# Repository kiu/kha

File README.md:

# kha

Overengineered Modular RS-485 Multi-Master 19" Subrack Home Control

## Repository

<sup>Hint: "bgt" is German for [Baugruppenträger](https://de.wikipedia.org/wiki/Baugruppentr%C3%A4ger) translating to subrack assembly</sup>

- [datasheets](datasheets/): Datasheets of used components and rack dimensions / layouts
- [kha-bgt-misc](kha-bgt-misc/): Generic subrack modules
- [kha-bgt-rack](kha-bgt-rack/): 19" rack assembly
- [kha-bgt-subrack](kha-bgt-subrack/): Subrack modules
- [kha-boot.X](kha-boot.X/): Bootloader used by all devices ([main.c](kha-boot.X/main.c))
- [kha-common.X](kha-common.X/): Protocol stack used by all devices ([kha-stack.c](kha-common.X/kha-stack.c) / [kha-stack.h](kha-common.X/kha-stack.h) / [kha-constants.h](kha-common.X/kha-constants.h))
- [kha-nodes](kha-nodes/): Bus nodes
- [superseded](superseded/): Superseded ideas and failed hardware revisions
- [tools](tools/): Helper scripts to e.g. generate userrow data
- [kha-bom-collection.pdf](kha-bom-collection.pdf) / [.ods](kha-bom-collection.ods): Not exactly a Bill-of-Materials rather a collection of most components used
- [kha-protocol.pdf](kha-protocol.pdf) / [.ods](kha-protocol.ods): Protocol stack definitions

## Protocol

RS-485 at 500 kbaud (8N1), half duplex, every node may send. Commands, addresses and registers are listed in
[kha-protocol.ods](kha-protocol.ods).

### Frame

```
0x42 0x99 <len> <from> <to> <cmd> <payload ...> <crc>
```

- `0x42 0x99` starts a frame. Inside a frame every `0x42` is followed by an extra `0x66`, so `0x42 0x99` is
  always a start. The escape bytes are not counted and not part of the CRC.
- `len` counts len, from, to, cmd, payload and crc: 5 + payload, payload up to 67 bytes.
- CRC-8 (polynomial 0x31, init 0xFF, no final XOR) over all bytes from `len` to the last byte before the CRC.

### Bus access

- The stack counts 100 µs ticks on TCB2, which is reserved for the stack. Every falling edge on RX resets the
  count.
- A node sends once the bus has been quiet for 10 + its own address ticks (1 ms + address × 100 µs). Addresses
  are unique, so no two nodes wait for the same slot.
- After sending, a node waits once for the longest slot (10 + 0xF0 ticks), so the others get their turn first.
- The bootloader commands F9–FC skip the slot wait to keep flashing fast: send TX off (F0) to the other
  nodes before flashing.

### Firmware

- Flash: bootloader at 0x0000–0x3FFF, app at 0x4000–0xFFFF. At every boot a node computes a CRC-32 over
  0x4000–0xFFFF (without the final XOR) and reports it with the boot and app versions in its UP (E2) and
  ident (E1).
- Bootloader: after a reset it waits 4 s for bootloader commands (FD keeps it there), then starts the app.
  Brown-out detection at 2.85 V. No lock bits, so UPDI can read and write a node.
- Flashing over the bus: [kha_fw.py](tools/kha-scripts/); via UPDI: [kha_updi.py](tools/kha-scripts/).

## Bus health page

[kha-web](tools/kha-web/) shows the state of every node on a static web page: missing nodes, error
counters, days since the last reboot, and whether nodes of the same board type run the same firmware. A
collector follows the gateway's log passively, keeps the state in SQLite and exports a JSON file for the page.
Screenshot with mock data:

## Videos
Two hour deep dive lecture style video on youtube: https://youtu.be/BUSnTUGKZzc

## Photos

## Misc

- All PCBs use [eAVR](https://github.com/kiu/eAVR/) as connector for AVR flashing
- It all started simple with [lightdesk](https://github.com/kiu/lightdesk/)

## Todo

- Node: LED marquee node
- Node: IrDA bridge (bridging the bus through a window)
- Stack: Combine queued TX commands into single burst?
- Stack: Merge similiar queued TX commands into single command?
- Stack: Process TX commands as incoming RX commands?

## Regrets

- Terrible collision detection / avoidance
- Buck converter capacitor generates audible noise

# License

This project is licensed under the Creative Commons Attribution-NonCommercial 3.0 Unported (CC BY-NC 3.0) license.

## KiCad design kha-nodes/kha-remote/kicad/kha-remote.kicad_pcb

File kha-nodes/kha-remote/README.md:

# kha-remote

433Mhz and IR Remote

## Photos

## Render

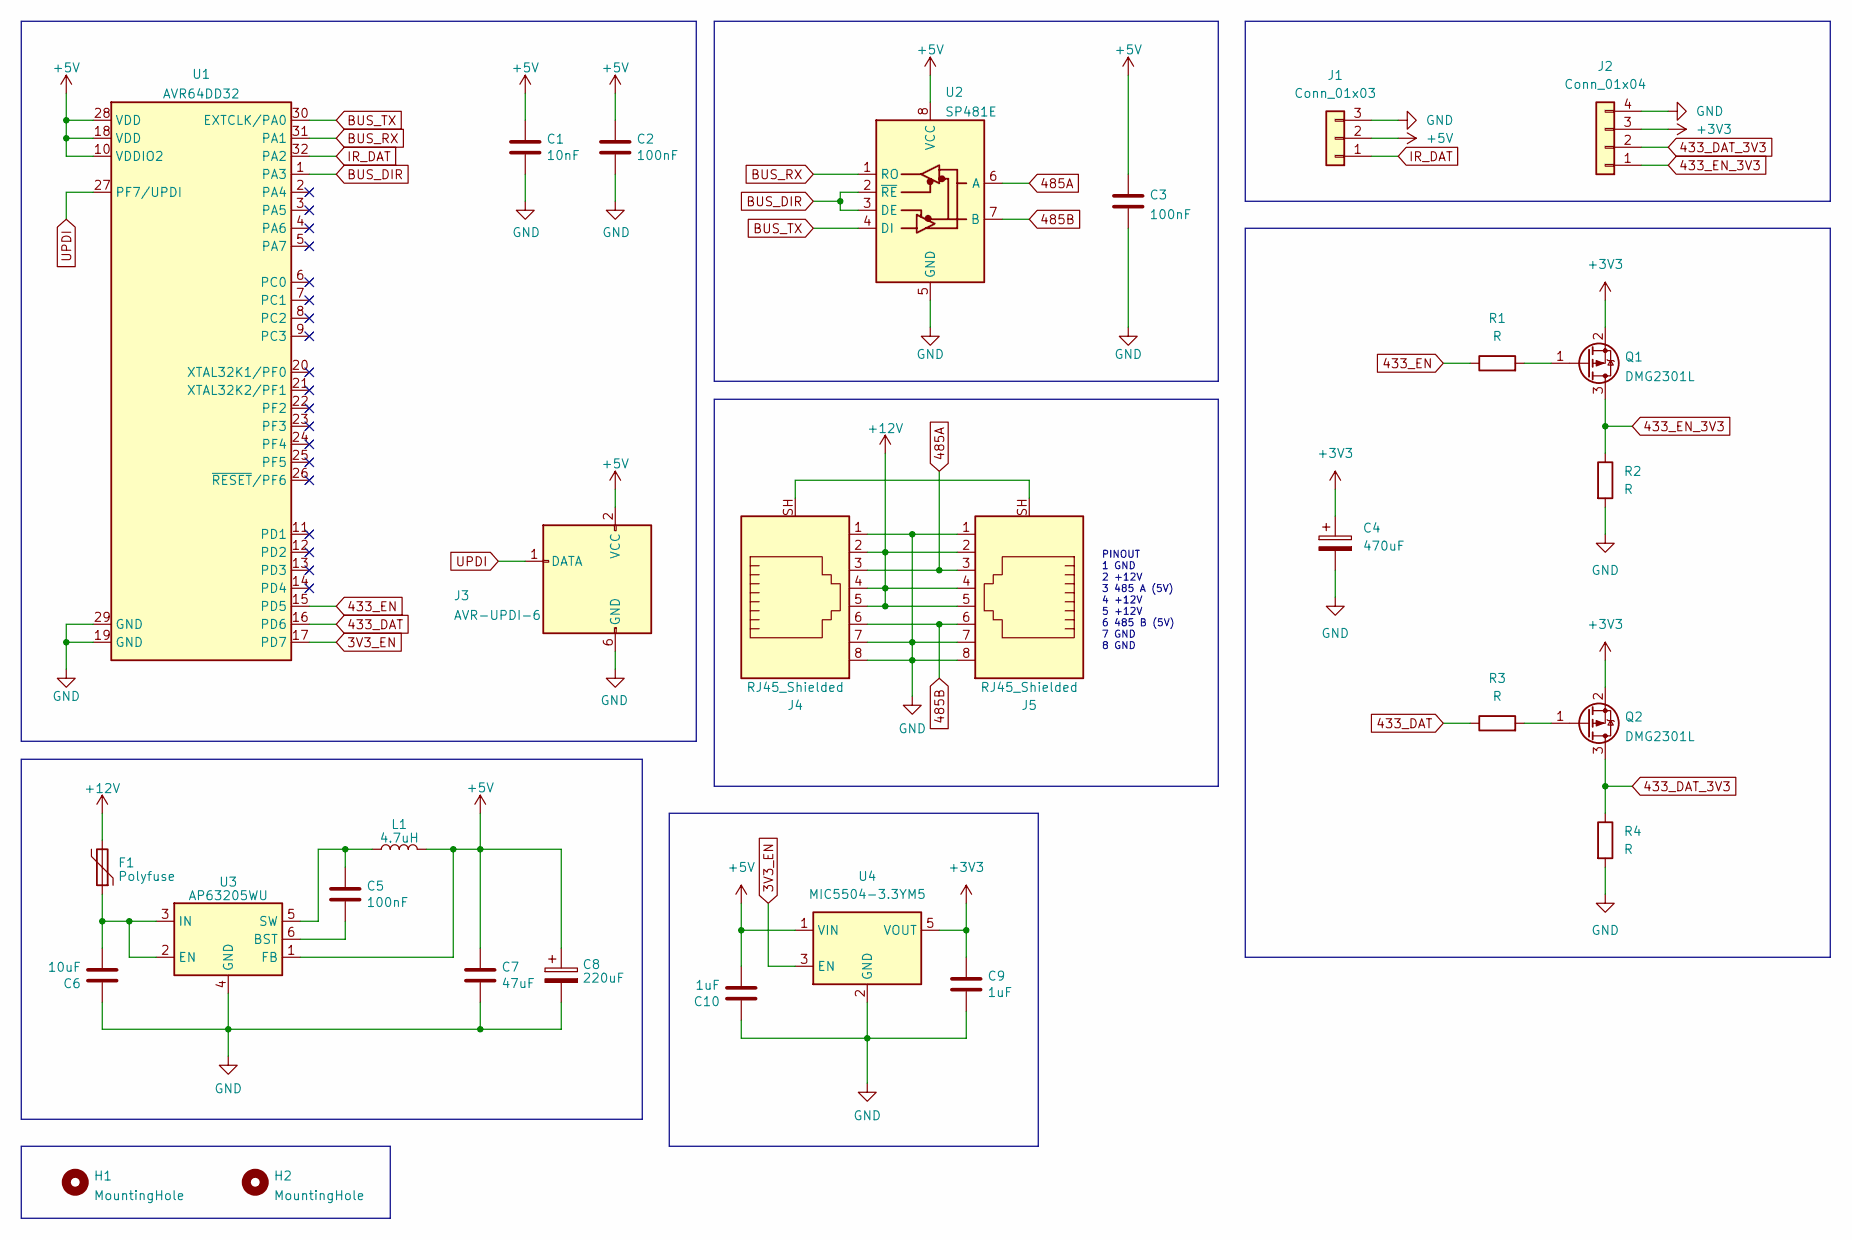
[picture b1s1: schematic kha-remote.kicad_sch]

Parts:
C1: 10nF; C_0805_2012Metric
C2, C3, C5: 100nF; C_0805_2012Metric
C4: 470uF; CP_Elec_6.3x7.7
C6: 10uF; C_0805_2012Metric
C7: 47uF; C_1210_3225Metric
C8: 220uF; CP_EIA-6032-28_Kemet-C
C9, C10: 1uF; C_0805_2012Metric
F1: Polyfuse; Fuse_0805_2012Metric
H1, H2: MountingHole; MountingHole_3.2mm_M3_DIN965
J1: Conn_01x03; TerminalBlock_Phoenix_MKDS-1,5-3-5.08_1x03_P5.08mm_Horizont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
J2: Conn_01x04; PinSocket_1x04_P2.54mm_Vertical
J3: AVR-UPDI-6; eAVR6-UPDI-F
J4, J5: RJ45_Shielded; GDLX-S-88K
L1: 4.7uH; L_1210_3225Metric
Q1, Q2: DMG2301L; SOT-23
R1, R2, R3, R4: R; R_0805_2012Metric
U1: AVR64DD32; TQFP-32_7x7mm_P0.8mm
U2: SP481E; SOIC-8_3.9x4.9mm_P1.27mm
U3: AP63205WU; TSOT-23-6
U4: MIC5504-3.3YM5; SOT-23-5

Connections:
3V3_EN: U1.17 (PD7), U4.3 (EN)
433_DAT: R3.1, U1.16 (PD6)
433_DAT_3V3: J2.2, Q2.3 (D), R4.1
433_EN: R1.1, U1.15 (PD5)
433_EN_3V3: J2.1, Q1.3 (D), R2.1
485A: J4.3, J5.3, U2.6 (A)
485B: J4.6, J5.6, U2.7 (B)
+3V3: C4.1, C9.1, J2.3, Q1.2 (S), Q2.2 (S), U4.5 (VOUT)
+5V: C1.1, C2.1, C3.1, C7.1, C8.1, C10.2, J1.2, J3.2 (VCC), L1.2, U1.10 (VDDIO2), U1.18 (VDD), U1.28 (VDD), U2.8 (VCC), U3.1 (FB), U4.1 (VIN)
+12V: F1.2, J4.2, J4.4, J4.5, J5.2, J5.4, J5.5
BUS_DIR: U1.1 (PA3), U2.2 (~RE), U2.3 (DE)
BUS_RX: U1.31 (PA1), U2.1 (RO)
BUS_TX: U1.30 (EXTCLK/PA0), U2.4 (DI)
GND: C1.2, C2.2, C3.2, C4.2, C6.1, C7.2, C8.2, C9.2, C10.1, J1.3, J2.4, J3.6 (GND), J4.1, J4.7, J4.8, J5.1, J5.7, J5.8, R2.2, R4.2, U1.19 (GND), U1.29 (GND), U2.5 (GND), U3.4 (GND), U4.2 (GND)
IR_DAT: J1.1, U1.32 (PA2)
unnamed: J4.SH, J5.SH
unnamed: Q1.1 (G), R1.2
unnamed: Q2.1 (G), R3.2
unnamed: C5.2, U3.6 (BST)
unnamed: C6.2, F1.1, U3.2 (EN), U3.3 (IN)
unnamed: C5.1, L1.1, U3.5 (SW)
UPDI: J3.1 (DATA), U1.27 (PF7/UPDI)

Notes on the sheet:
PINOUT 1 GND 2 +12V 3 485 A (5V) 4 +12V 5 +12V 6 485 B (5V) 7 GND 8 GND

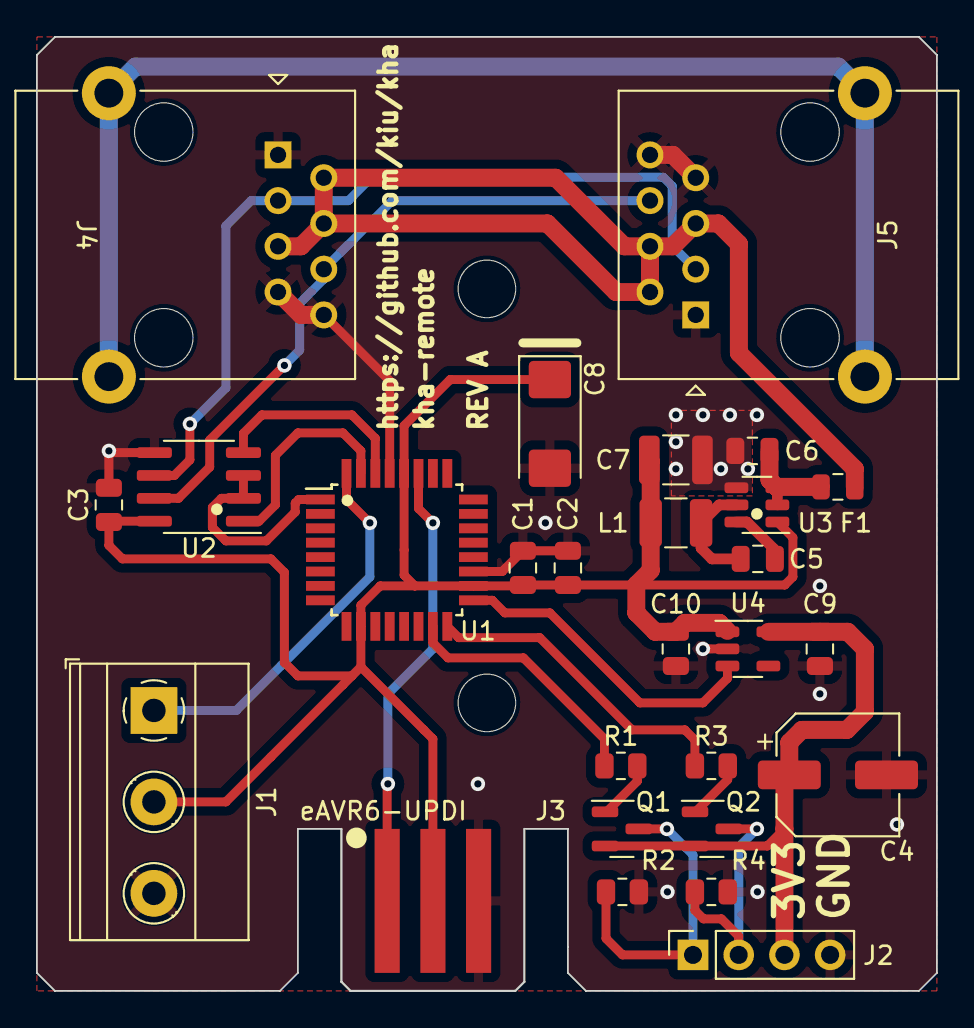
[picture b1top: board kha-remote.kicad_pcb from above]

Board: 2 copper layers, 50.0 x 53.0 mm, 29 parts (0 on the bottom side), 22 nets.

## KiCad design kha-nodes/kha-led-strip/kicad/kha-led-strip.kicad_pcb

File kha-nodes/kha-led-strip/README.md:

# kha-led-strip

LED Strip Node

## Photos

## Render

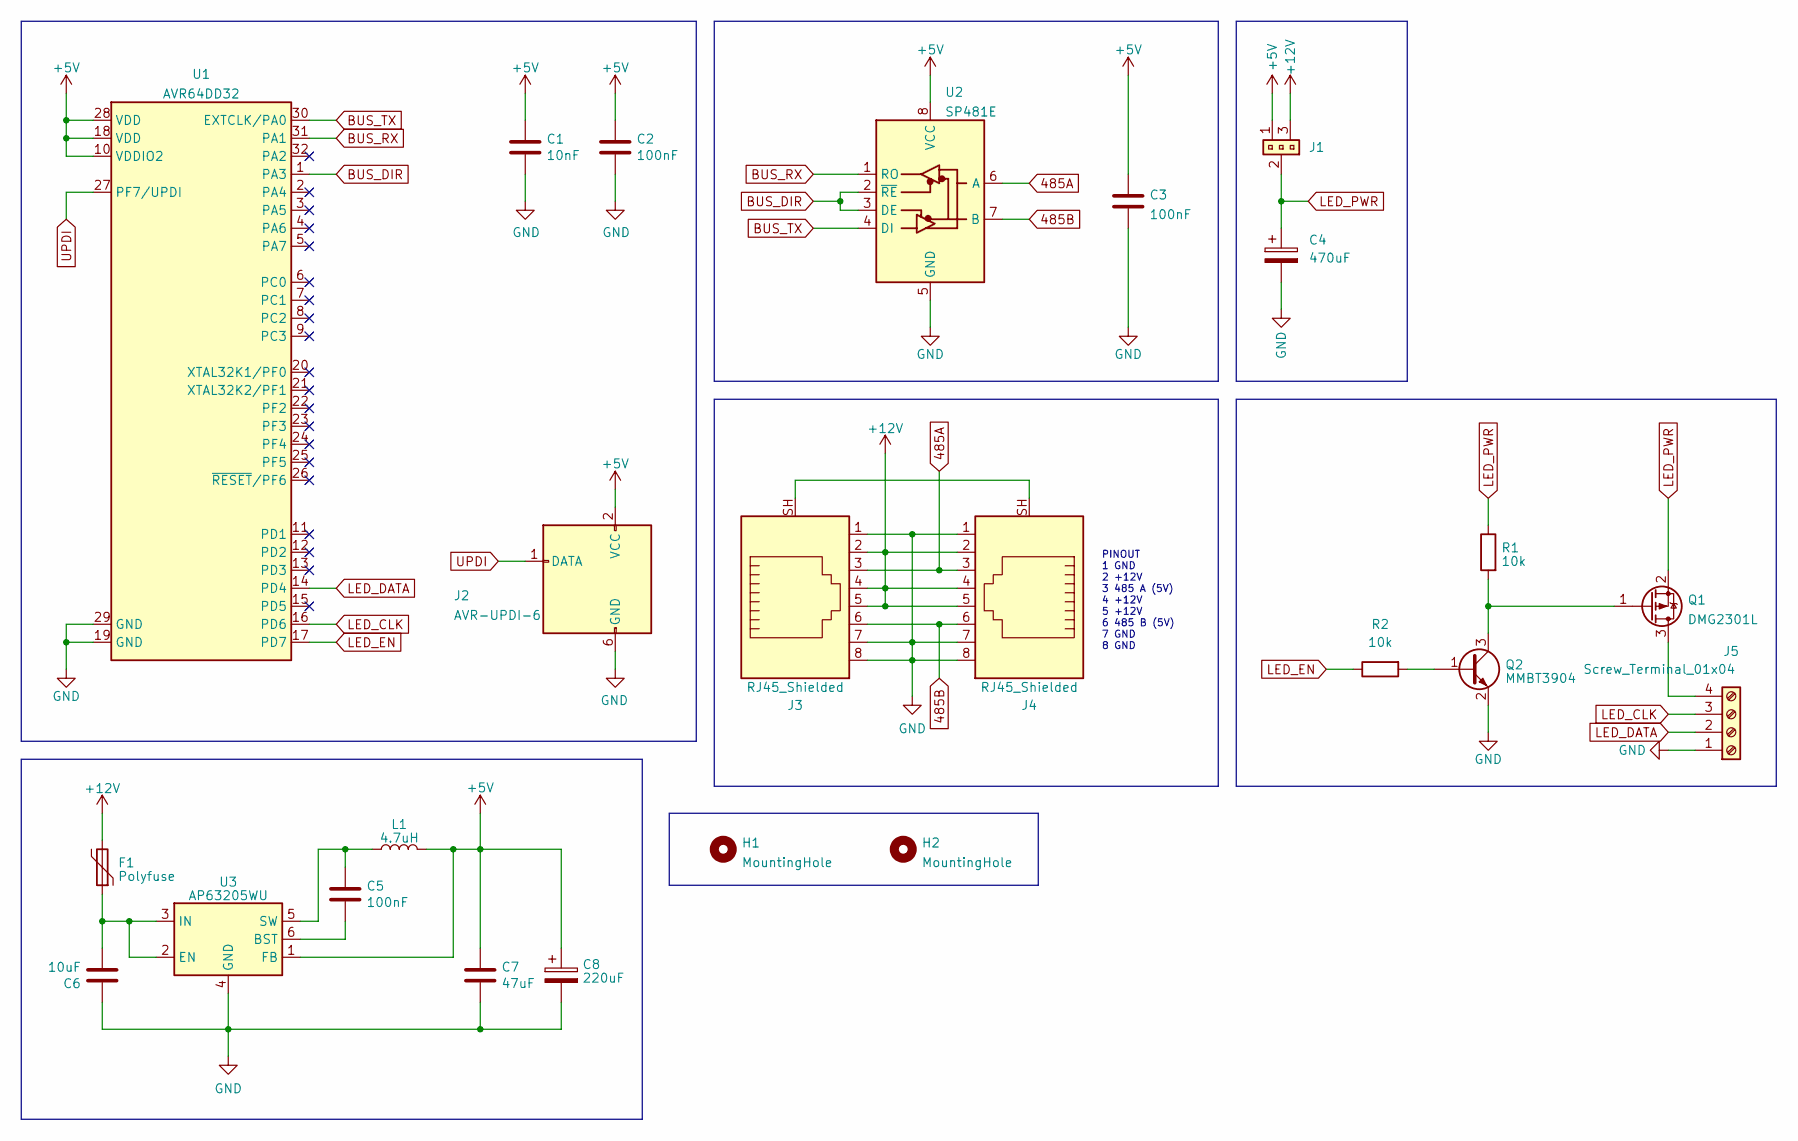
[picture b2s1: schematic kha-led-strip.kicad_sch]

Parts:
C1: 10nF; C_0805_2012Metric
C2, C3, C5: 100nF; C_0805_2012Metric
C4: 470uF; CP_Elec_8x10.5
C6: 10uF; C_0805_2012Metric
C7: 47uF; C_1210_3225Metric
C8: 220uF; CP_EIA-6032-28_Kemet-C
F1: Polyfuse; Fuse_0805_2012Metric
H1, H2: MountingHole; MountingHole_3.2mm_M3_DIN965
J1: 1x03_Jumper; PinHeader_1x03_P2.54mm_Vertical
J2: AVR-UPDI-6; eAVR6-UPDI-F
J3, J4: RJ45_Shielded; GDLX-S-88K
J5: Screw_Terminal_01x04; TerminalBlock_Phoenix_MKDS-1,5-4-5.08_1x04_P5.08mm_Horizont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
L1: 4.7uH; L_1210_3225Metric
Q1: DMG2301L; SOT-23
Q2: MMBT3904; SOT-23
R1, R2: 10k; R_0805_2012Metric
U1: AVR64DD32; TQFP-32_7x7mm_P0.8mm
U2: SP481E; SOIC-8_3.9x4.9mm_P1.27mm
U3: AP63205WU; TSOT-23-6

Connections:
485A: J3.3, J4.3, U2.6 (A)
485B: J3.6, J4.6, U2.7 (B)
+5V: C1.1, C2.1, C3.1, C7.1, C8.1, J1.1, J2.2 (VCC), L1.2, U1.10 (VDDIO2), U1.18 (VDD), U1.28 (VDD), U2.8 (VCC), U3.1 (FB)
+12V: F1.2, J1.3, J3.2, J3.4, J3.5, J4.2, J4.4, J4.5
BUS_DIR: U1.1 (PA3), U2.2 (~RE), U2.3 (DE)
BUS_RX: U1.31 (PA1), U2.1 (RO)
BUS_TX: U1.30 (EXTCLK/PA0), U2.4 (DI)
GND: C1.2, C2.2, C3.2, C4.2, C6.1, C7.2, C8.2, J2.6 (GND), J3.1, J3.7, J3.8, J4.1, J4.7, J4.8, J5.1, Q2.2 (E), U1.19 (GND), U1.29 (GND), U2.5 (GND), U3.4 (GND)
LED_CLK: J5.3, U1.16 (PD6)
LED_DATA: J5.2, U1.14 (PD4)
LED_EN: R2.1, U1.17 (PD7)
LED_PWR: C4.1, J1.2, Q1.2 (S), R1.1
unnamed: J3.SH, J4.SH
unnamed: J5.4, Q1.3 (D)
unnamed: Q1.1 (G), Q2.3 (C), R1.2
unnamed: Q2.1 (B), R2.2
unnamed: C5.2, U3.6 (BST)
unnamed: C6.2, F1.1, U3.2 (EN), U3.3 (IN)
unnamed: C5.1, L1.1, U3.5 (SW)
UPDI: J2.1 (DATA), U1.27 (PF7/UPDI)

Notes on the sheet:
PINOUT 1 GND 2 +12V 3 485 A (5V) 4 +12V 5 +12V 6 485 B (5V) 7 GND 8 GND

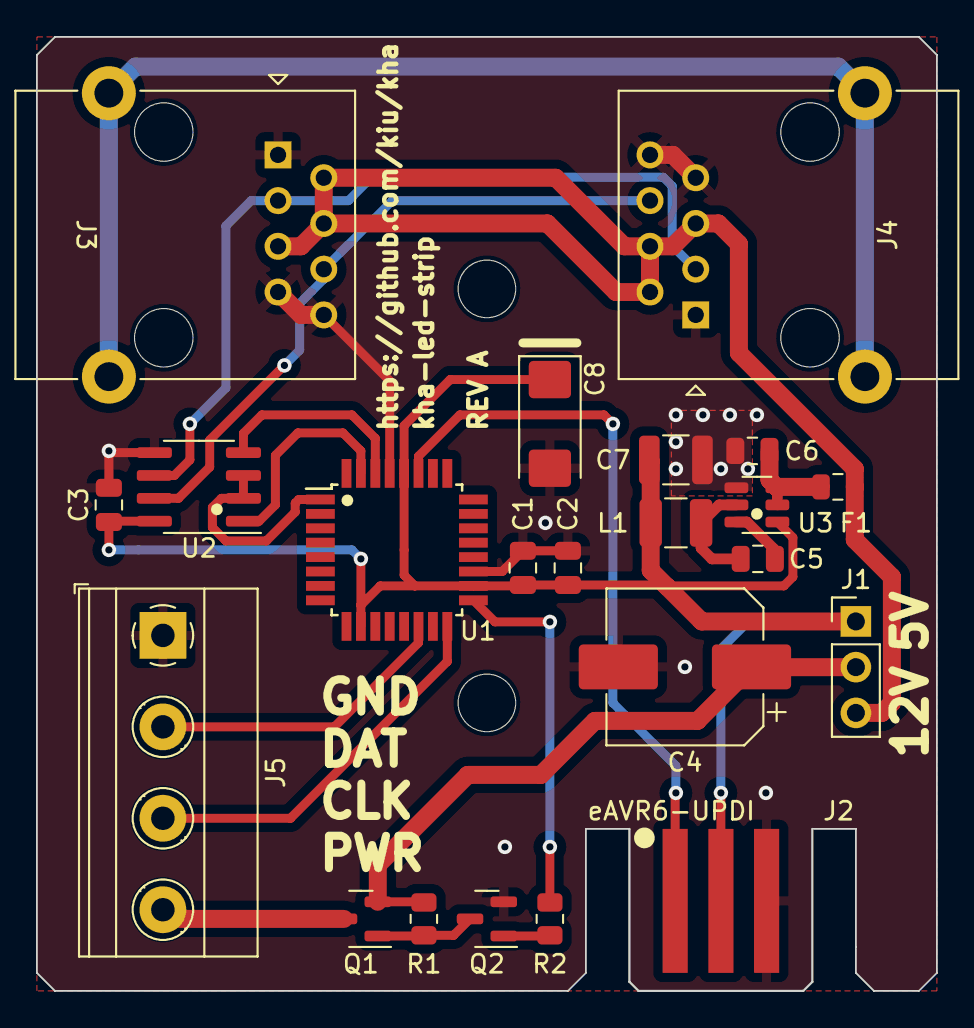
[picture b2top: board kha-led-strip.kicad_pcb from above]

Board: 2 copper layers, 50.0 x 53.0 mm, 24 parts (0 on the bottom side), 20 nets.

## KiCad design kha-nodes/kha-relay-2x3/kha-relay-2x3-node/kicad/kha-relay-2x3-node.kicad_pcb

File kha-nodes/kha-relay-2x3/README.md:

# kha-relay-2x3

Mains Power Relay

## Photos

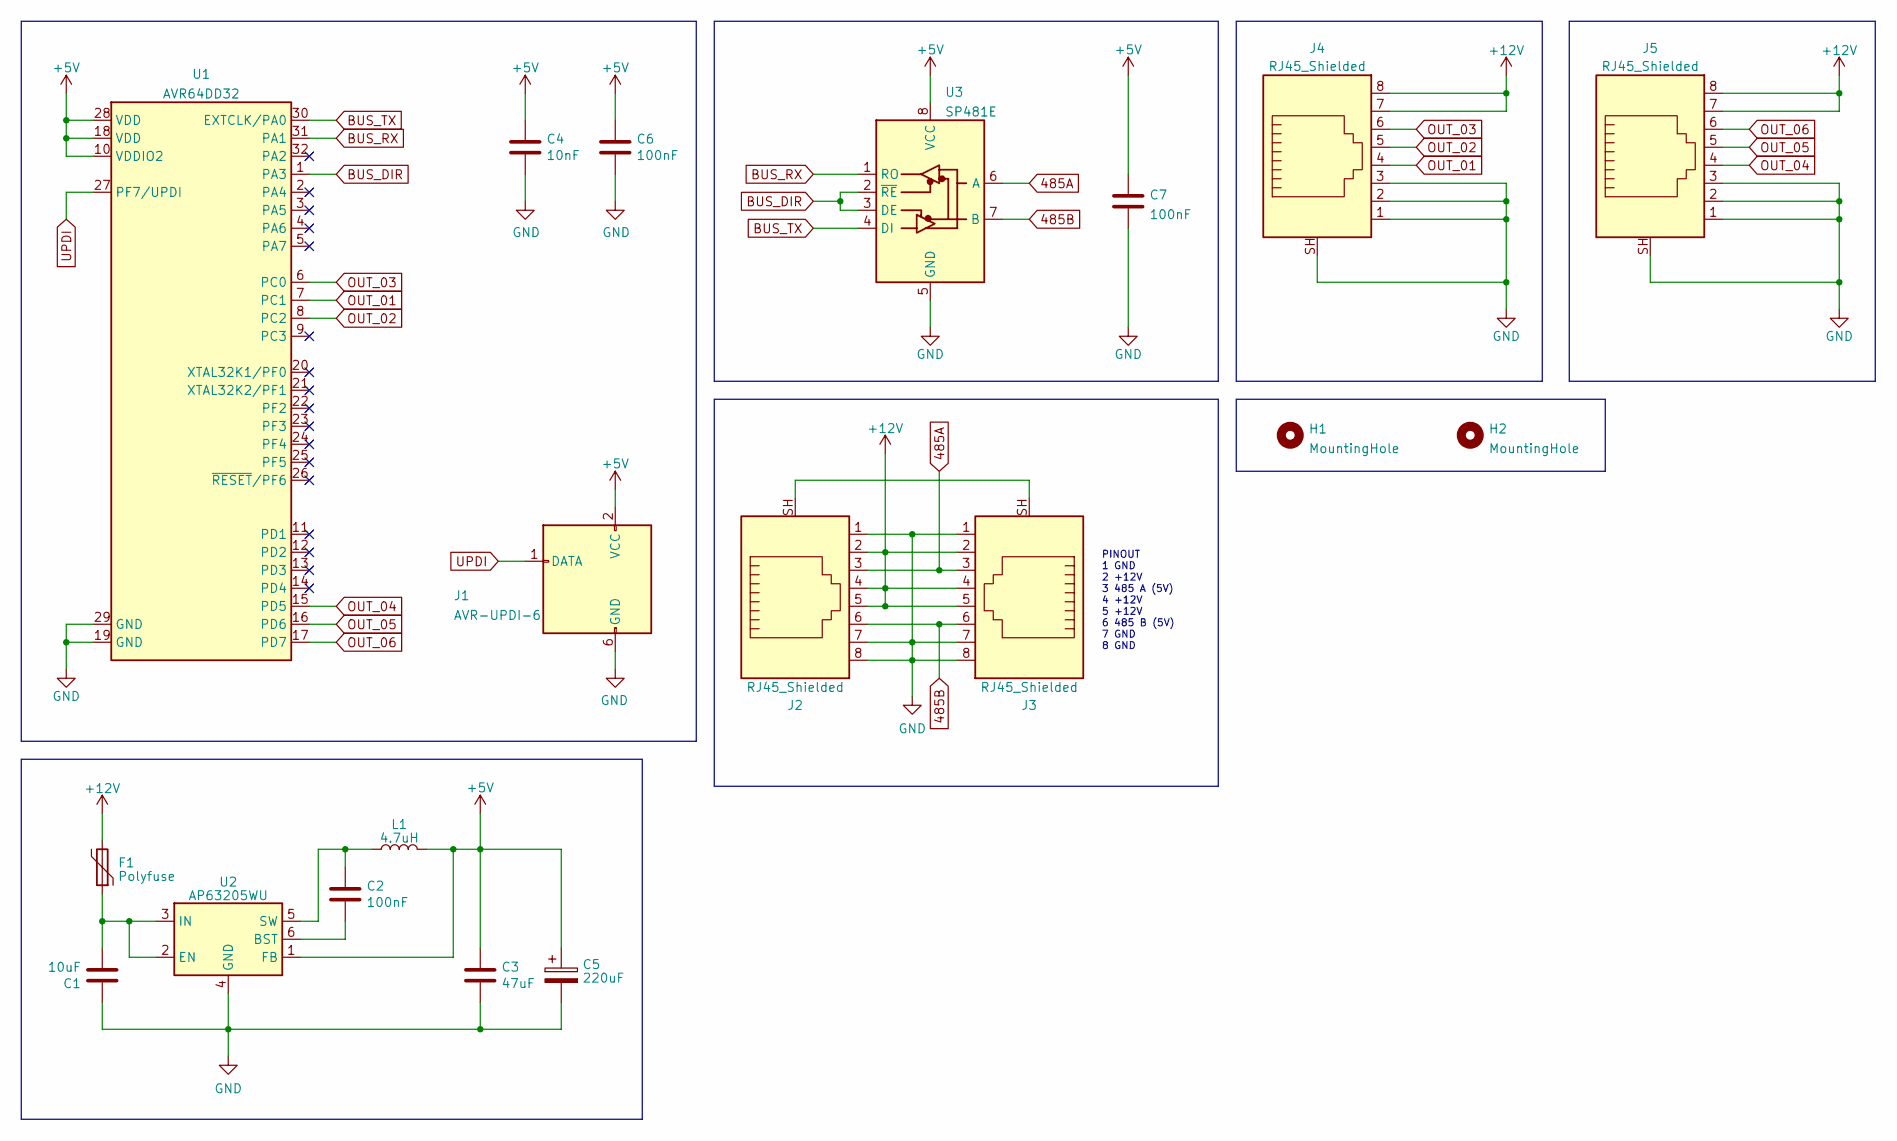
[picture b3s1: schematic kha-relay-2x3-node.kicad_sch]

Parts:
C1: 10uF; C_0805_2012Metric
C2, C6, C7: 100nF; C_0805_2012Metric
C3: 47uF; C_1210_3225Metric
C4: 10nF; C_0805_2012Metric
C5: 220uF; CP_EIA-6032-28_Kemet-C
F1: Polyfuse; Fuse_0805_2012Metric
H1, H2: MountingHole; MountingHole_3.2mm_M3_DIN965
J1: AVR-UPDI-6; eAVR6-UPDI-F
J2, J3, J4, J5: RJ45_Shielded; GDLX-S-88K
L1: 4.7uH; L_1210_3225Metric
U1: AVR64DD32; TQFP-32_7x7mm_P0.8mm
U2: AP63205WU; TSOT-23-6
U3: SP481E; SOIC-8_3.9x4.9mm_P1.27mm

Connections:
485A: J2.3, J3.3, U3.6 (A)
485B: J2.6, J3.6, U3.7 (B)
+5V: C3.1, C4.1, C5.1, C6.1, C7.1, J1.2 (VCC), L1.2, U1.10 (VDDIO2), U1.18 (VDD), U1.28 (VDD), U2.1 (FB), U3.8 (VCC)
+12V: F1.2, J2.2, J2.4, J2.5, J3.2, J3.4, J3.5, J4.7, J4.8, J5.7, J5.8
BUS_DIR: U1.1 (PA3), U3.2 (~RE), U3.3 (DE)
BUS_RX: U1.31 (PA1), U3.1 (RO)
BUS_TX: U1.30 (EXTCLK/PA0), U3.4 (DI)
GND: C1.1, C3.2, C4.2, C5.2, C6.2, C7.2, J1.6 (GND), J2.1, J2.7, J2.8, J3.1, J3.7, J3.8, J4.1, J4.2, J4.3, J4.SH, J5.1, J5.2, J5.3, J5.SH, U1.19 (GND), U1.29 (GND), U2.4 (GND), U3.5 (GND)
unnamed: J2.SH, J3.SH
unnamed: C2.2, U2.6 (BST)
unnamed: C1.2, F1.1, U2.2 (EN), U2.3 (IN)
unnamed: C2.1, L1.1, U2.5 (SW)
OUT_01: J4.4, U1.7 (PC1)
OUT_02: J4.5, U1.8 (PC2)
OUT_03: J4.6, U1.6 (PC0)
OUT_04: J5.4, U1.15 (PD5)
OUT_05: J5.5, U1.16 (PD6)
OUT_06: J5.6, U1.17 (PD7)
UPDI: J1.1 (DATA), U1.27 (PF7/UPDI)

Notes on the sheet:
PINOUT 1 GND 2 +12V 3 485 A (5V) 4 +12V 5 +12V 6 485 B (5V) 7 GND 8 GND

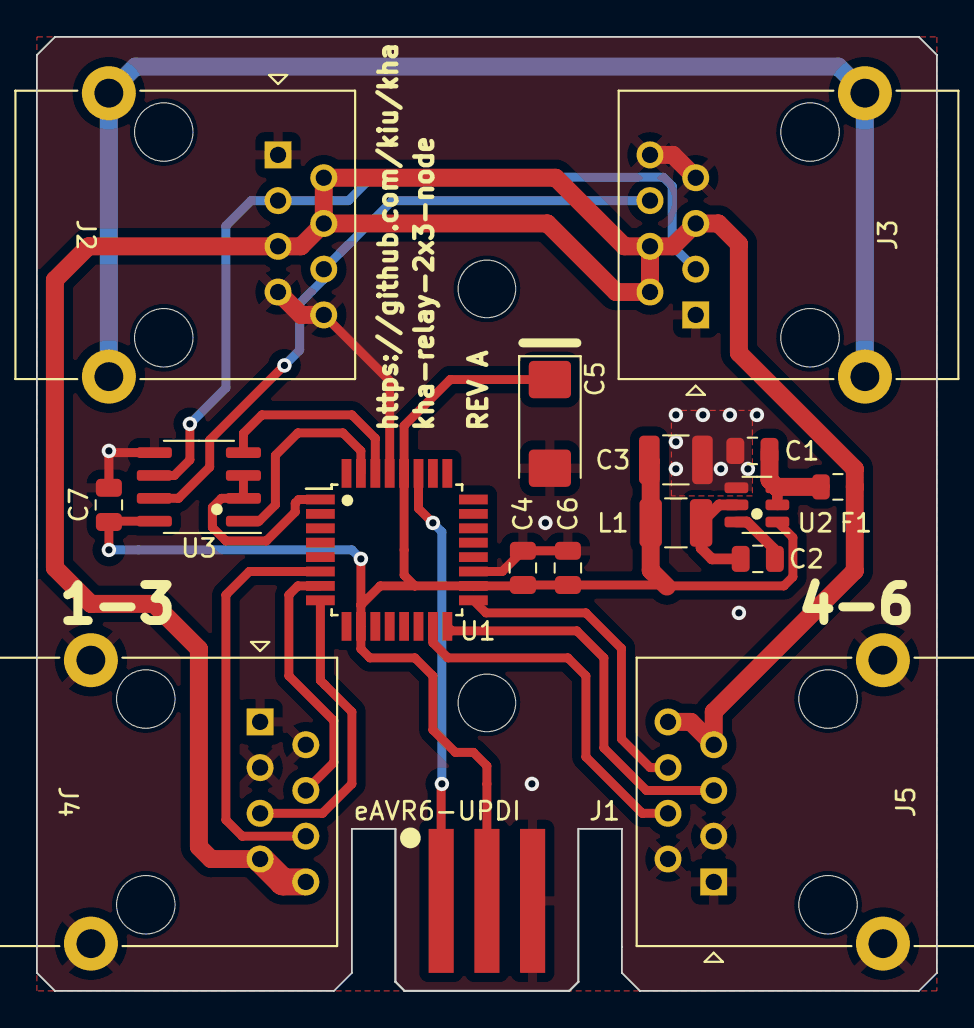
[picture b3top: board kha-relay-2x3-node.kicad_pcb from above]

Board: 2 copper layers, 50.0 x 53.0 mm, 19 parts (0 on the bottom side), 19 nets.

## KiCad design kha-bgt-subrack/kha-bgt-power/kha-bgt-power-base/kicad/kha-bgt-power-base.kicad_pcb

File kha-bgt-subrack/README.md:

# kha-bgt-subrack

Subrack modules

## Photos

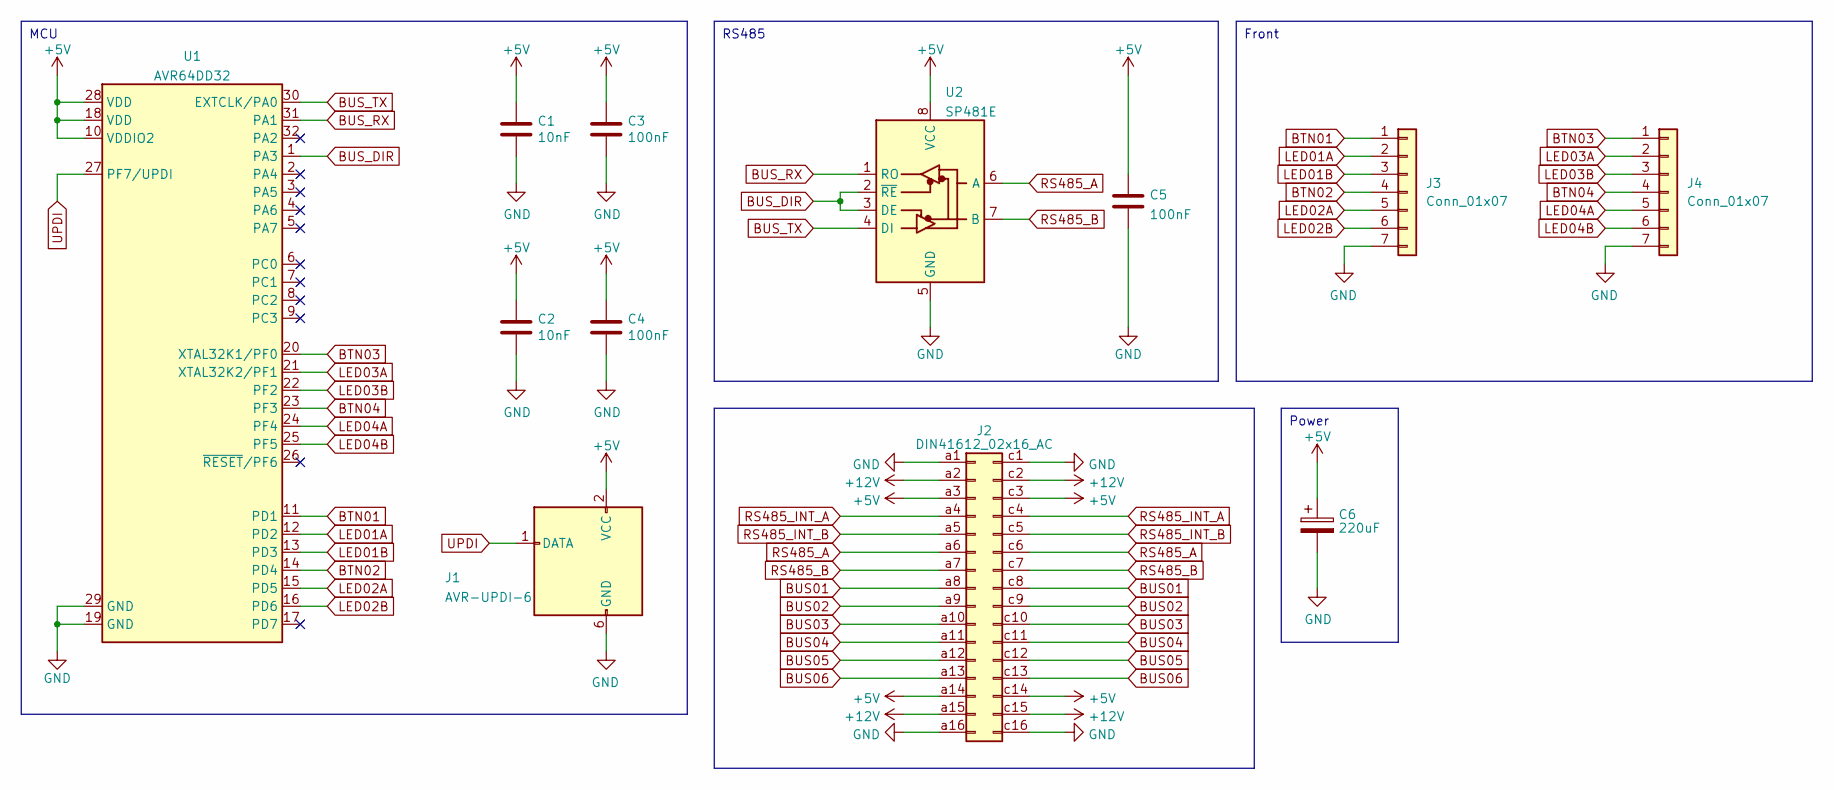
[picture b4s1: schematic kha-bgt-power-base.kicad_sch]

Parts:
C1, C2: 10nF; C_0805_2012Metric
C3, C4, C5: 100nF; C_0805_2012Metric
C6: 220uF; CP_EIA-6032-28_Kemet-C
J1: AVR-UPDI-6; eAVR6-UPDI-F
J2: DIN41612_02x16_AC; DIN41612_C2_2x16_Male_Horizontal_THT
J3, J4: Conn_01x07; JST_PH_B7B-PH-K_1x07_P2.00mm_Vertical
U1: AVR64DD32; TQFP-32_7x7mm_P0.8mm
U2: SP481E; SOIC-8_3.9x4.9mm_P1.27mm

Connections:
+5V: C1.1, C2.1, C3.1, C4.1, C5.1, C6.1, J1.2 (VCC), J2.a3, J2.a14, J2.c3, J2.c14, U1.10 (VDDIO2), U1.18 (VDD), U1.28 (VDD), U2.8 (VCC)
+12V: J2.a2, J2.a15, J2.c2, J2.c15
BTN01: J3.1, U1.11 (PD1)
BTN02: J3.4, U1.14 (PD4)
BTN03: J4.1, U1.20 (XTAL32K1/PF0)
BTN04: J4.4, U1.23 (PF3)
BT_CON: U1.5 (PA7)
BT_LNK: U1.8 (PC2)
BT_RX: U1.6 (PC0)
BT_TX: U1.7 (PC1)
BUS01: J2.a8, J2.c8
BUS02: J2.a9, J2.c9
BUS03: J2.a10, J2.c10
BUS04: J2.a11, J2.c11
BUS05: J2.a12, J2.c12
BUS06: J2.a13, J2.c13
BUS_DIR: U1.1 (PA3), U2.2 (~RE), U2.3 (DE)
BUS_RX: U1.31 (PA1), U2.1 (RO)
BUS_TX: U1.30 (EXTCLK/PA0), U2.4 (DI)
GND: C1.2, C2.2, C3.2, C4.2, C5.2, C6.2, J1.6 (GND), J2.a1, J2.a16, J2.c1, J2.c16, J3.7, J4.7, U1.19 (GND), U1.29 (GND), U2.5 (GND)
LED01A: J3.2, U1.12 (PD2)
LED01B: J3.3, U1.13 (PD3)
LED02A: J3.5, U1.15 (PD5)
LED02B: J3.6, U1.16 (PD6)
LED03A: J4.2, U1.21 (XTAL32K2/PF1)
LED03B: J4.3, U1.22 (PF2)
LED04A: J4.5, U1.24 (PF4)
LED04B: J4.6, U1.25 (PF5)
RS485_A: J2.a6, J2.c6, U2.6 (A)
RS485_B: J2.a7, J2.c7, U2.7 (B)
RS485_INT_A: J2.a4, J2.c4
RS485_INT_B: J2.a5, J2.c5
SR01: U1.4 (PA6)
SR02: U1.2 (PA4)
SR03: U1.3 (PA5)
S_BT_VCC: U1.9 (PC3)
UPDI: J1.1 (DATA), U1.27 (PF7/UPDI)

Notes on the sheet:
Front
Power
RS485
MCU

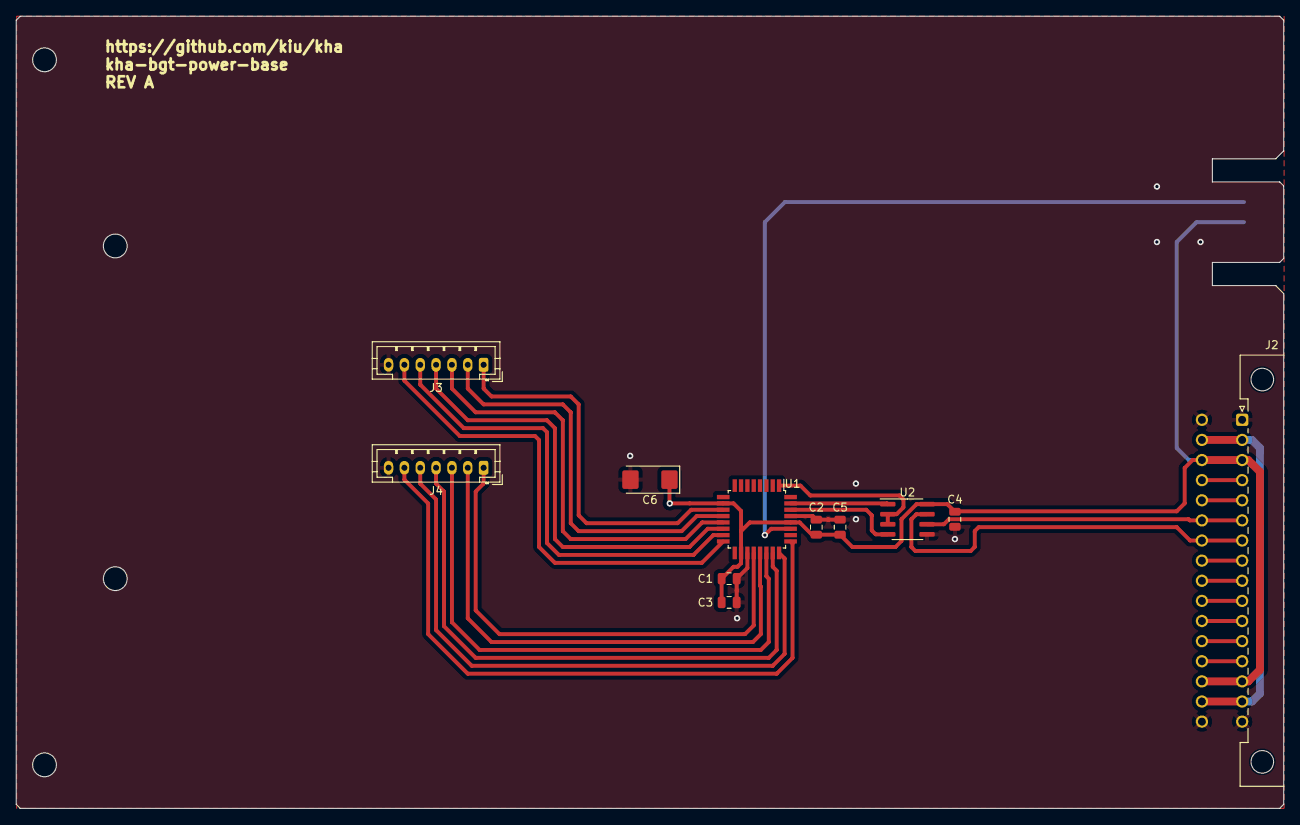
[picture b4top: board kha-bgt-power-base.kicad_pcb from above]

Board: 2 copper layers, 160.0 x 100.0 mm, 12 parts (1 on the bottom side), 29 nets.

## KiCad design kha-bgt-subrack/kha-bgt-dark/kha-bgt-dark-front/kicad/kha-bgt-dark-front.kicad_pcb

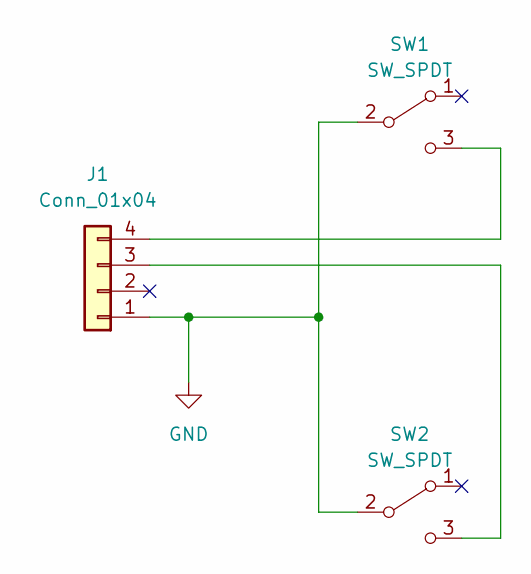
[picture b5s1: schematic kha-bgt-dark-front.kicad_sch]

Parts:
J1: Conn_01x04; JST_PH_B4B-PH-SM4-TB_1x04-1MP_P2.00mm_Vertical
SW1, SW2: SW_SPDT; PB86

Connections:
GND: J1.1, SW1.2 (B), SW2.2 (B)
unnamed: J1.3, SW2.3 (C)
unnamed: J1.4, SW1.3 (C)

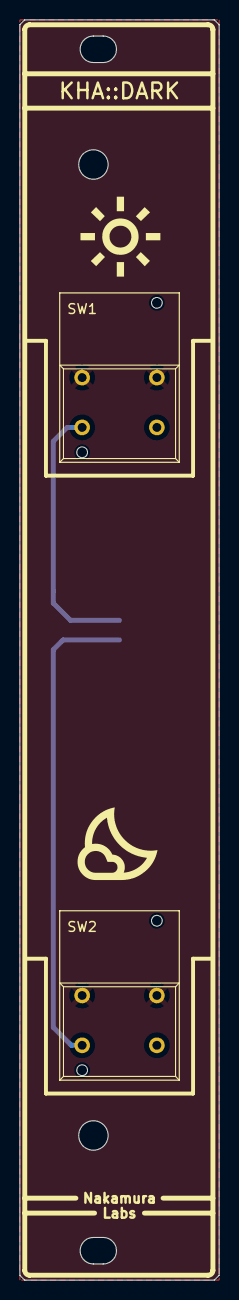
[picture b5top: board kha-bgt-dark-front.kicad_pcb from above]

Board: 2 copper layers, 20.3 x 128.5 mm, 3 parts (1 on the bottom side), 3 nets.

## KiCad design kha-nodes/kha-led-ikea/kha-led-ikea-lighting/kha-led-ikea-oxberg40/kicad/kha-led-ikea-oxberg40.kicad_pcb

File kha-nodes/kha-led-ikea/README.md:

# kha-led-ikea-lighting

IKEA LED Panels and Termination

## Photos

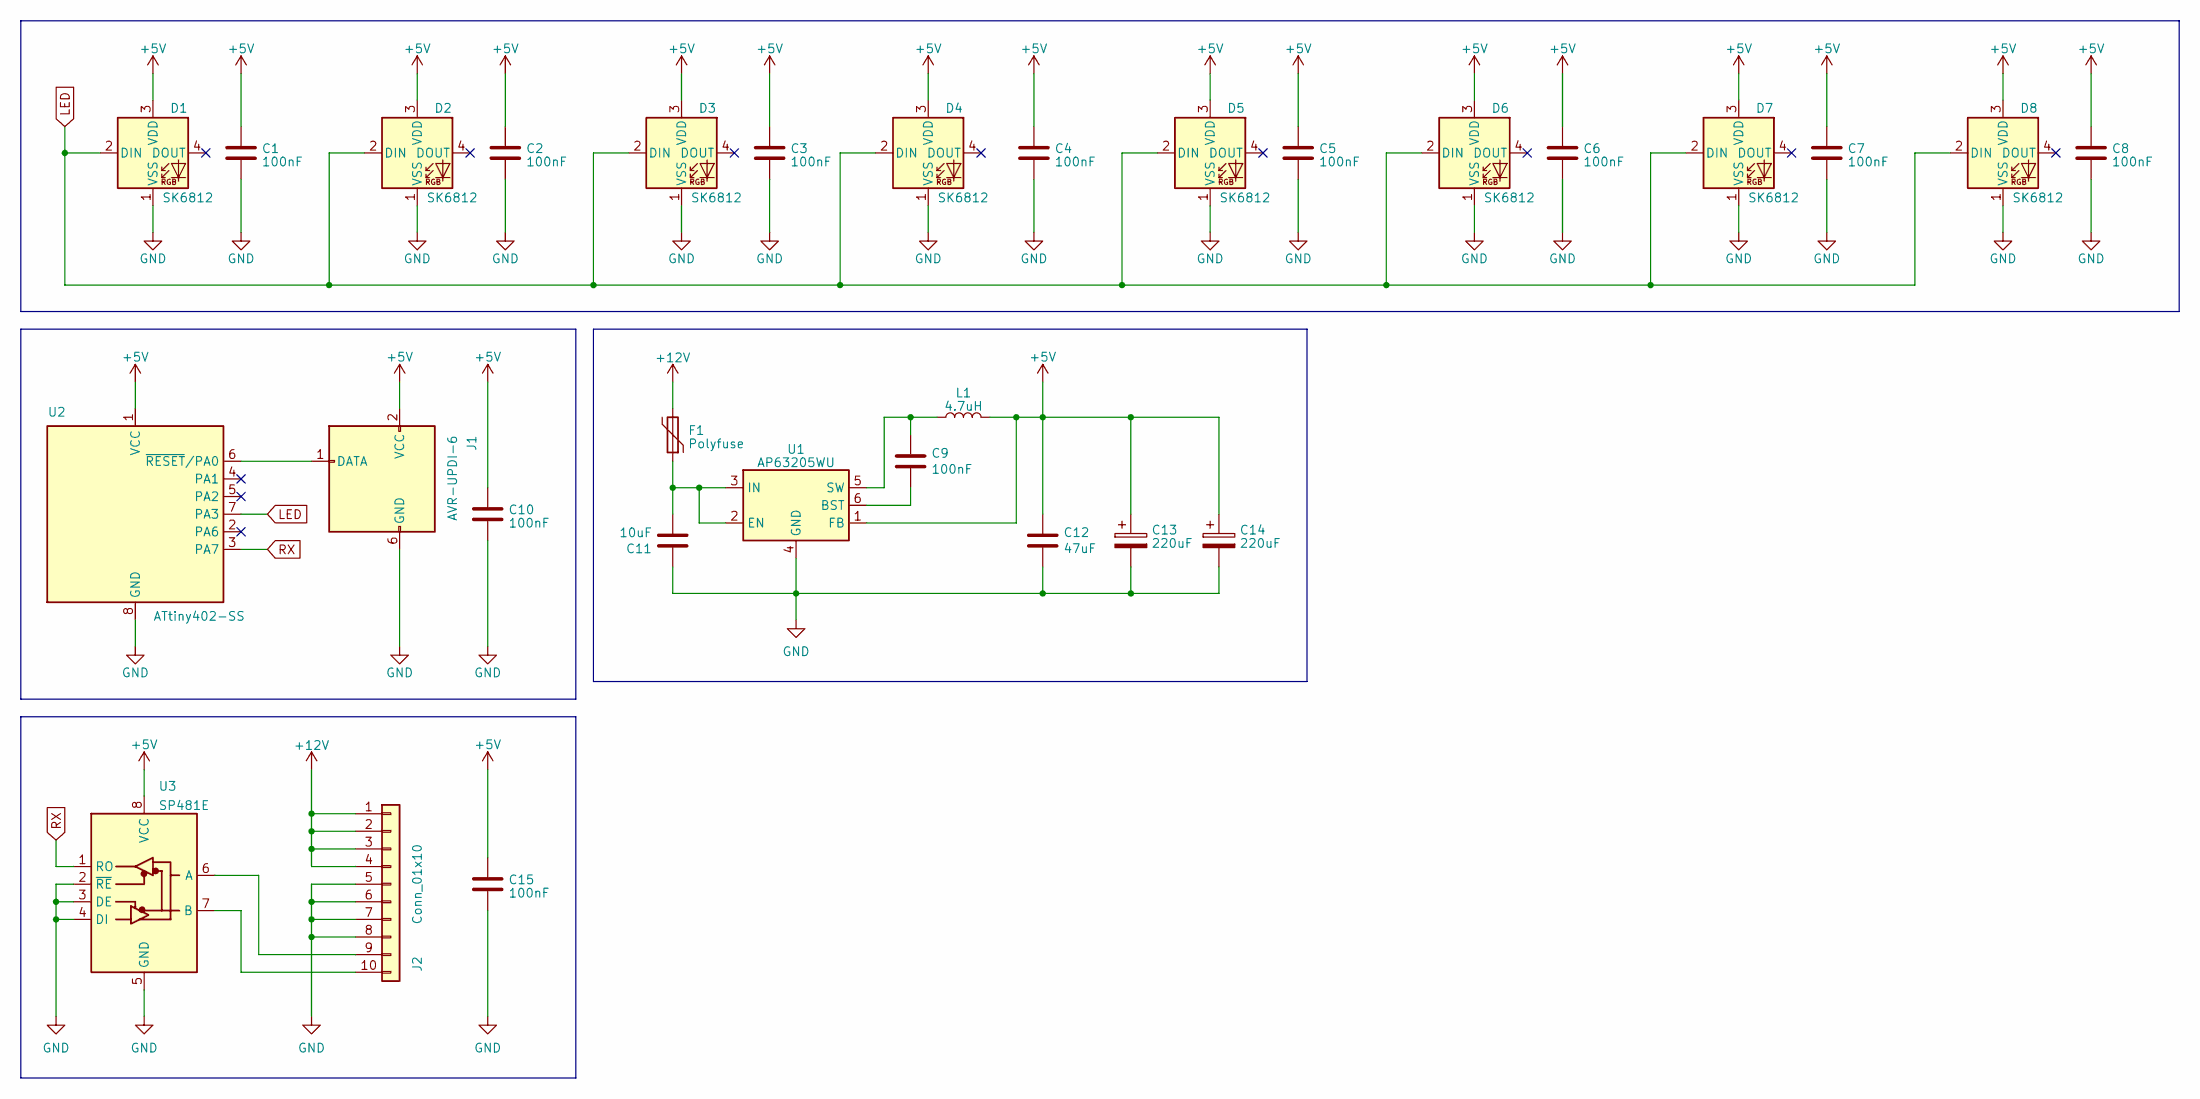
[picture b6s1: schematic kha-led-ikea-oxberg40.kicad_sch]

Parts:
C1, C2, C3, C4, C5, C6, C7, C8, C9, C10, C15: 100nF; C_0805_2012Metric
C11: 10uF; C_0805_2012Metric
C12: 47uF; C_1210_3225Metric
C13, C14: 220uF; CP_EIA-6032-28_Kemet-C
D1, D2, D3, D4, D5, D6, D7, D8: SK6812; LED_SK6812_PLCC4_5.0x5.0mm_P3.2mm
F1: Polyfuse; Fuse_0805_2012Metric
J1: AVR-UPDI-6; IDC-Header_2x03_P2.54mm_Vertical_SMD
J2: Conn_01x10; IDC-Header_2x05_P2.54mm_Vertical_SMD
L1: 4.7uH; L_1210_3225Metric
U1: AP63205WU; TSOT-23-6
U2: ATtiny402-SS; SOIC-8_3.9x4.9mm_P1.27mm
U3: SP481E; SOIC-8_3.9x4.9mm_P1.27mm

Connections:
+5V: C1.1, C2.1, C3.1, C4.1, C5.1, C6.1, C7.1, C8.1, C10.1, C12.1, C13.1, C14.1, C15.1, D1.3 (VDD), D2.3 (VDD), D3.3 (VDD), D4.3 (VDD), D5.3 (VDD), D6.3 (VDD), D7.3 (VDD), D8.3 (VDD), J1.2 (VCC), L1.2, U1.1 (FB), U2.1 (VCC), U3.8 (VCC)
+12V: F1.2, J2.1, J2.2, J2.3, J2.4
GND: C1.2, C2.2, C3.2, C4.2, C5.2, C6.2, C7.2, C8.2, C10.2, C11.1, C12.2, C13.2, C14.2, C15.2, D1.1 (VSS), D2.1 (VSS), D3.1 (VSS), D4.1 (VSS), D5.1 (VSS), D6.1 (VSS), D7.1 (VSS), D8.1 (VSS), J1.6 (GND), J2.5, J2.6, J2.7, J2.8, U1.4 (GND), U2.8 (GND), U3.2 (~RE), U3.3 (DE), U3.4 (DI), U3.5 (GND)
LED: D1.2 (DIN), D2.2 (DIN), D3.2 (DIN), D4.2 (DIN), D5.2 (DIN), D6.2 (DIN), D7.2 (DIN), D8.2 (DIN), U2.7 (PA3)
unnamed: J1.1 (DATA), U2.6 (~RESET/PA0)
unnamed: J2.9, U3.6 (A)
unnamed: J2.10, U3.7 (B)
unnamed: C9.2, U1.6 (BST)
unnamed: C11.2, F1.1, U1.2 (EN), U1.3 (IN)
unnamed: C9.1, L1.1, U1.5 (SW)
RX: U2.3 (PA7), U3.1 (RO)

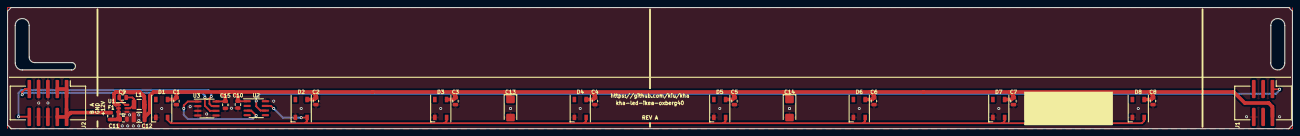
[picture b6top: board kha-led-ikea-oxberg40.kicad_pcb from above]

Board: 2 copper layers, 350.0 x 33.0 mm, 30 parts (0 on the bottom side), 11 nets.

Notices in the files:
kha-bgt-subrack/kha-bgt-audio/kha-bgt-audio.X/mcc_generated_files/system/pins.h:
© [2024] Microchip Technology Inc. and its subsidiaries.
